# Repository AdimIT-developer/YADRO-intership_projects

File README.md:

# YADRO-intership_projects
- KiCad

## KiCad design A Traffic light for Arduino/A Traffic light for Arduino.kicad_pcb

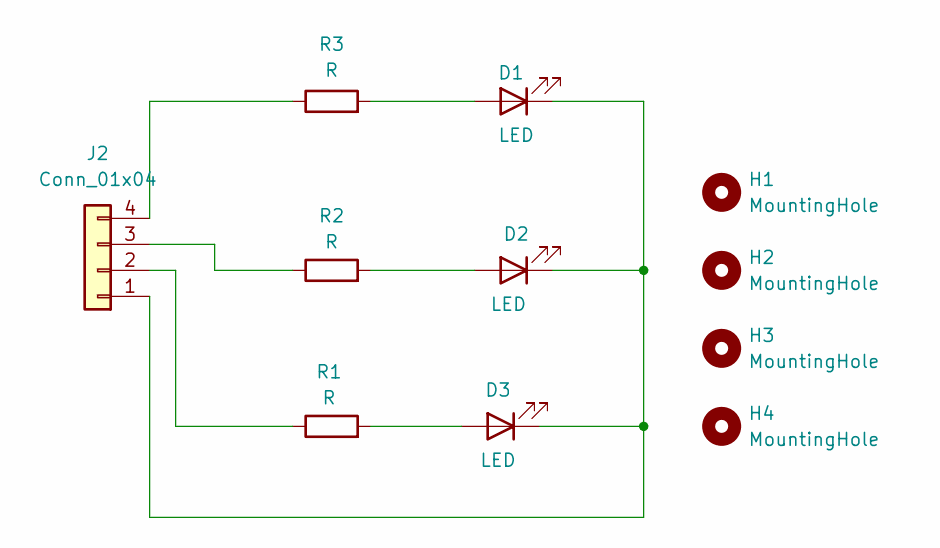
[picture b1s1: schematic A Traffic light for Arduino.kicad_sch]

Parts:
D1, D2, D3: LED; LED_D3.0mm
H1, H2, H3, H4: MountingHole; MountingHole_2.5mm_Pad
J2: Conn_01x04; PinHeader_1x04_P2.54mm_Horizontal
R1, R2, R3: R; R_Axial_DIN0204_L3.6mm_D1.6mm_P5.08mm_Horizontal

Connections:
unnamed: D1.2 (A), R3.2
unnamed: D1.1 (K), D2.1 (K), D3.1 (K), J2.1
unnamed: D2.2 (A), R2.2
unnamed: D3.2 (A), R1.2
unnamed: J2.2, R1.1
unnamed: J2.3, R2.1
unnamed: J2.4, R3.1

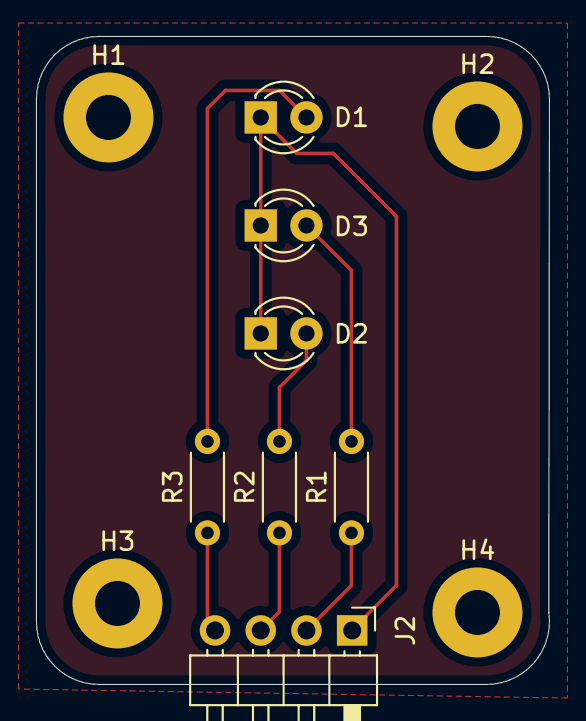
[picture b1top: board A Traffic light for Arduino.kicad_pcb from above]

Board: 2 copper layers, 28.5 x 36.0 mm, 11 parts (0 on the bottom side), 7 nets.
